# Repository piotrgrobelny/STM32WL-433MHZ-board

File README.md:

# STM32WL-433MHZ-board
STM32WL developer board with RF antenna. The board is made to work with LoRa, GFSK, GMSK, BPSK in 433MHz frequency. 
STM32WLE5CCU6 with single code Cortex-M4 256KB Flash and 64KB RAM is used. The project is based on different boards like Nucleo and BB-STM32WL. Feel free to use, but i don't promise that it will work. 

## Features
- STM32WLE5CCU6 Single code 32-bit Arm Cortex-M4
- RF transceiver 433MHz
- USB power supply
- SWD connector
- RESET button
- Two user buttons
- Two user leds
- Voltage regulator based on TLV70233
- Dimensions 5.2cm x 7.3cm

## Files description 
- `Board photos` 3D renders and PCB signal paths
- `KiCad` KiCad project with PCB, schematics, gerber files, list of elements and library of footprints
- `Documentantation` Project schematic in pdf, STM32WL datasheets and Nucleo and BB-STM32WL schematics

#### Front of PCB

#### Back of PCB

#### Upper signal path

#### Lower signal path

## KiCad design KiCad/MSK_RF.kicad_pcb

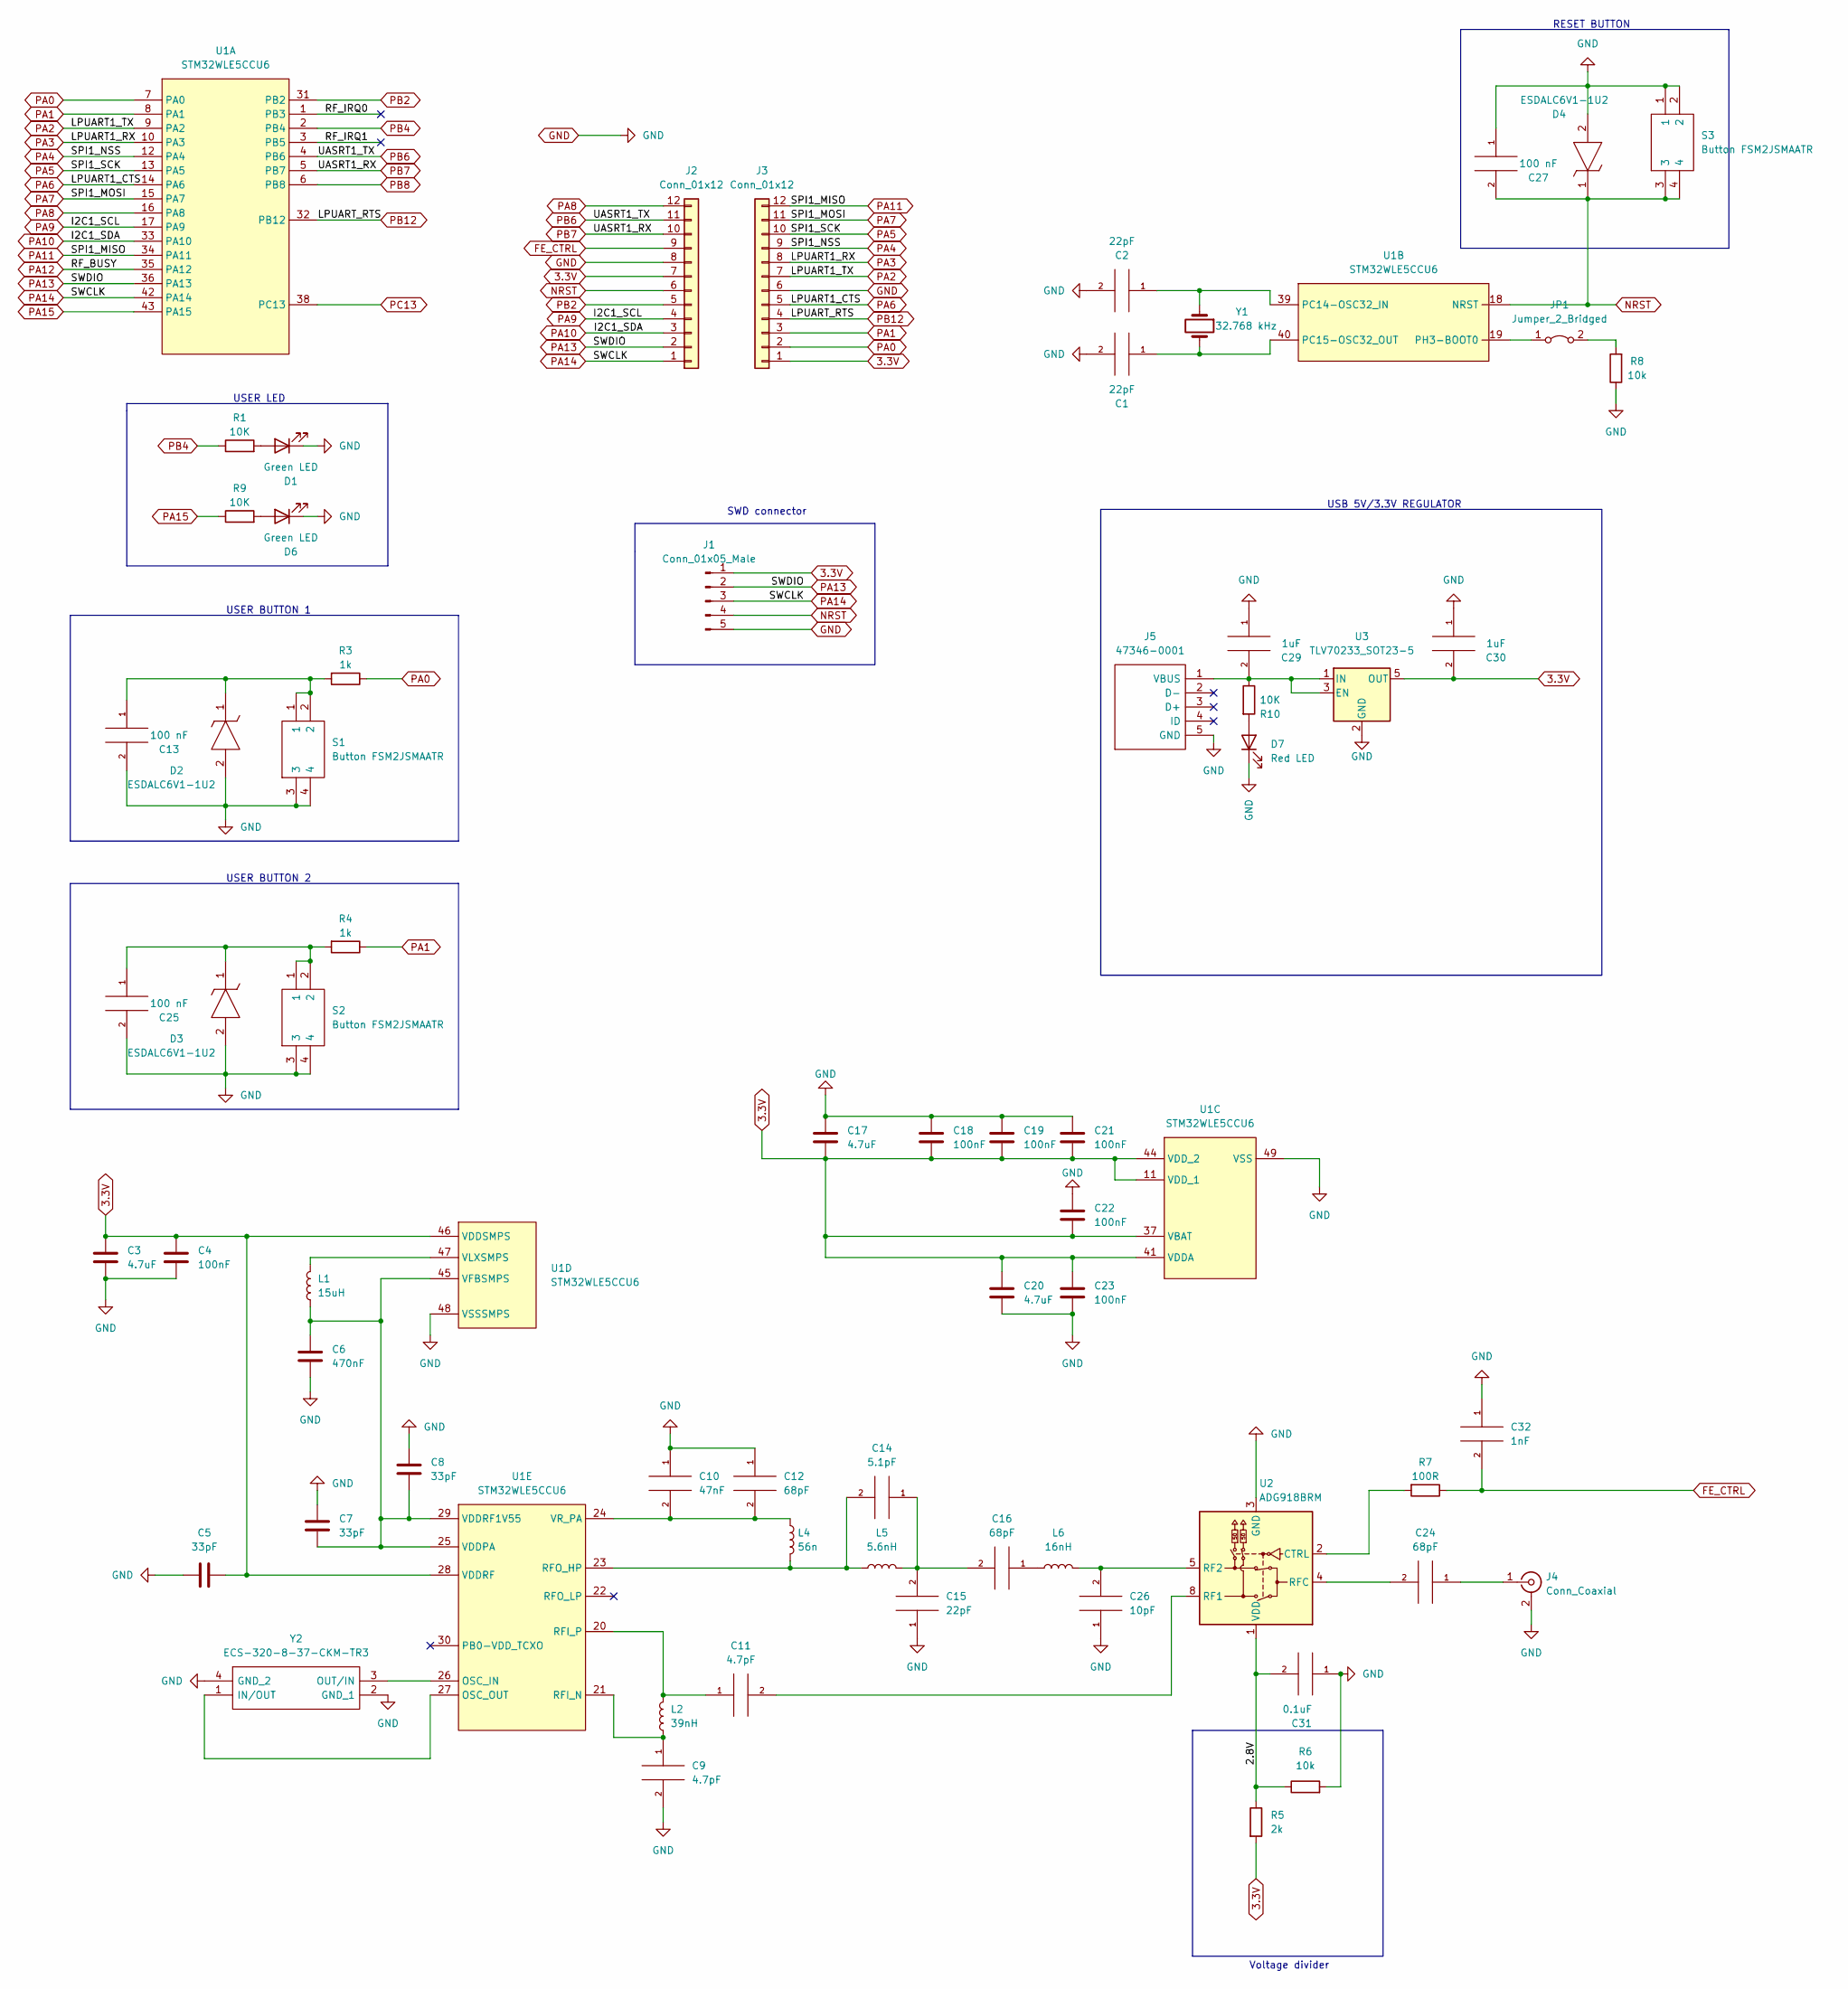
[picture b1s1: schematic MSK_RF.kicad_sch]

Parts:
C1, C2: 22pF; CP_Elec_3x5.3
C3, C17, C20: 4.7uF; C_0603_1608Metric_Pad1.08x0.95mm_HandSolder
C4, C18, C19, C21, C22, C23: 100nF; C_0603_1608Metric_Pad1.08x0.95mm_HandSolder
C5, C7, C8: 33pF; C_0603_1608Metric_Pad1.08x0.95mm_HandSolder
C6: 470nF; C_0603_1608Metric_Pad1.08x0.95mm_HandSolder
C9, C11: 4.7pF; C_0603_1608Metric_Pad1.08x0.95mm_HandSolder
C10: 47nF; C_0603_1608Metric_Pad1.08x0.95mm_HandSolder
C12, C16, C24: 68pF; C_0603_1608Metric_Pad1.08x0.95mm_HandSolder
C13, C25, C27: 100 nF; C_0603_1608Metric_Pad1.08x0.95mm_HandSolder
C14: 5.1pF; C_0603_1608Metric_Pad1.08x0.95mm_HandSolder
C15: 22pF; C_0603_1608Metric_Pad1.08x0.95mm_HandSolder
C26: 10pF; C_0603_1608Metric_Pad1.08x0.95mm_HandSolder
C29, C30: 1uF; C_0603_1608Metric_Pad1.08x0.95mm_HandSolder
C31: 0.1uF; C_0603_1608Metric_Pad1.08x0.95mm_HandSolder
C32: 1nF; C_0603_1608Metric_Pad1.08x0.95mm_HandSolder
D1, D6: Green LED; LED_0603_1608Metric_Pad1.05x0.95mm_HandSolder
D2, D3, D4: ESDALC6V1-1U2; ESDALC6V11U2; Mouser Part Number 511-ESDALC6V1-1U2
D7: Red LED; LED_0603_1608Metric_Pad1.05x0.95mm_HandSolder
J1: Conn_01x05_Male; PinHeader_1x05_P2.54mm_Vertical
J2, J3: Conn_01x12; PinSocket_1x12_P2.54mm_Vertical
J4: Conn_Coaxial; SMA_Molex_73251-1153_EdgeMount_Horizontal
J5: 47346-0001; Mouser Part Number 538-47346-0001
JP1: Jumper_2_Bridged; PinHeader_1x02_P2.54mm_Vertical
L1: 15uH; L_0603_1608Metric_Pad1.05x0.95mm_HandSolder
L2: 39nH; L_0603_1608Metric_Pad1.05x0.95mm_HandSolder
L4: 56n; L_0603_1608Metric_Pad1.05x0.95mm_HandSolder
L5: 5.6nH; L_0603_1608Metric_Pad1.05x0.95mm_HandSolder
L6: 16nH; L_0603_1608Metric_Pad1.05x0.95mm_HandSolder
R1, R9, R10: 10K; R_0603_1608Metric_Pad0.98x0.95mm_HandSolder
R3, R4: 1k; R_0603_1608Metric_Pad0.98x0.95mm_HandSolder
R5: 2k; R_0603_1608Metric_Pad0.98x0.95mm_HandSolder
R6, R8: 10k; R_0603_1608Metric_Pad0.98x0.95mm_HandSolder
R7: 100R; R_0603_1608Metric_Pad0.98x0.95mm_HandSolder
S1, S2, S3: Button FSM2JSMAATR; FSM2J_1; Mouser Part Number 506-FSM2JSMAATR
U1: STM32WLE5CCU6; QFN50P700X700X60-49N-D
U2: ADG918BRM; MSOP-8_3x3mm_P0.65mm
U3: TLV70233_SOT23-5; SOT-23-5
Y1: 32.768 kHz; ECX-31B
Y2: ECS-320-8-37-CKM-TR3; ECS320837CKMTR3; Mouser Part Number 520-ECS-320837CKMTR3

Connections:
3.3V: C3.1, C4.1, C5.1, C17.2, C18.2, C19.2, C20.1, C21.2, C22.2, C23.1, C30.2, J1.1, J2.7, J3.1, R5.2, U1.11 (VDD_1), U1.28 (VDDRF), U1.37 (VBAT), U1.41 (VDDA), U1.44 (VDD_2), U1.46 (VDDSMPS), U3.5 (OUT)
/2.8V: C31.2, R5.1, R6.1, U2.1 (VDD)
/RF_IRQ0: U1.1 (PB3)
/RF_IRQ1: U1.3 (PB5)
FE_CTRL: C32.2, J2.9, R7.1
GND: C1.2, C2.2, C3.2, C4.2, C5.2, C6.2, C7.1, C8.1, C9.2, C10.1, C12.1, C13.2, C15.1, C17.1, C18.1, C19.1, C20.2, C21.1, C22.1, C23.2, C25.2, C26.1, C27.1, C29.1, C30.1, C31.1, C32.1, D1.1 (K), D2.2, D3.2, D4.2, D6.1 (K), D7.1 (K), J1.5, J2.8, J3.6, J4.2 (Ext), J5.5 (GND), R6.2, R8.1, S1.3, S1.4, S2.3, S2.4, S3.1, S3.2, U1.48 (VSSSMPS), U1.49 (VSS), U2.3 (GND), U2.6 (GND), U2.7 (GND), U3.2 (GND), Y2.2 (GND_1), Y2.4 (GND_2)
NRST: C27.2, D4.1, J1.4, J2.6, S3.3, S3.4, U1.18 (NRST)
unnamed: C1.1, U1.40 (PC15-OSC32_OUT), Y1.2
unnamed: C2.1, U1.39 (PC14-OSC32_IN), Y1.1
unnamed: C6.1, C7.2, C8.2, L1.1, U1.25 (VDDPA), U1.29 (VDDRF1V55), U1.45 (VFBSMPS)
unnamed: C9.1, L2.1, U1.21 (RFI_N)
unnamed: C10.2, C12.2, L4.1, U1.24 (VR_PA)
unnamed: C11.1, L2.2, U1.20 (RFI_P)
unnamed: C11.2, U2.8 (RF1)
unnamed: C13.1, D2.1, R3.2, S1.1, S1.2
unnamed: C14.1, C15.2, C16.2, L5.2
unnamed: C14.2, L4.2, L5.1, U1.23 (RFO_HP)
unnamed: C16.1, L6.1
unnamed: C24.1, J4.1 (In)
unnamed: C24.2, U2.4 (RFC)
unnamed: C25.1, D3.1, R4.2, S2.1, S2.2
unnamed: C26.2, L6.2, U2.5 (RF2)
unnamed: C29.2, J5.1 (VBUS), R10.1, U3.1 (IN), U3.3 (EN)
unnamed: D1.2 (A), R1.2
unnamed: D6.2 (A), R9.2
unnamed: D7.2 (A), R10.2
unnamed: JP1.1 (A), U1.19 (PH3-BOOT0)
unnamed: JP1.2 (B), R8.2
unnamed: L1.2, U1.47 (VLXSMPS)
unnamed: R7.2, U2.2 (CTRL)
unnamed: U1.26 (OSC_IN), Y2.3 (OUT/IN)
unnamed: U1.27 (OSC_OUT), Y2.1 (IN/OUT)
PA0: J3.2, R3.1, U1.7 (PA0)
PA1: J3.3, R4.1, U1.8 (PA1)
PA2: J3.7, U1.9 (PA2)
PA3: J3.8, U1.10 (PA3)
PA4: J3.9, U1.12 (PA4)
PA5: J3.10, U1.13 (PA5)
PA6: J3.5, U1.14 (PA6)
PA7: J3.11, U1.15 (PA7)
PA8: J2.12, U1.16 (PA8)
PA9: J2.4, U1.17 (PA9)
PA10: J2.3, U1.33 (PA10)
PA11: J3.12, U1.34 (PA11)
PA12: U1.35 (PA12)
PA13: J1.2, J2.2, U1.36 (PA13)
PA14: J1.3, J2.1, U1.42 (PA14)
PA15: R9.1, U1.43 (PA15)
PB2: J2.5, U1.31 (PB2)
PB4: R1.1, U1.2 (PB4)
PB6: J2.11, U1.4 (PB6)
PB7: J2.10, U1.5 (PB7)
PB8: U1.6 (PB8)
PB12: J3.4, U1.32 (PB12)
PC13: U1.38 (PC13)

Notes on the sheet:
SWD connector
USER BUTTON 2
RESET BUTTON
USER LED
USB 5V/3.3V REGULATOR
USER BUTTON 1
Voltage divider

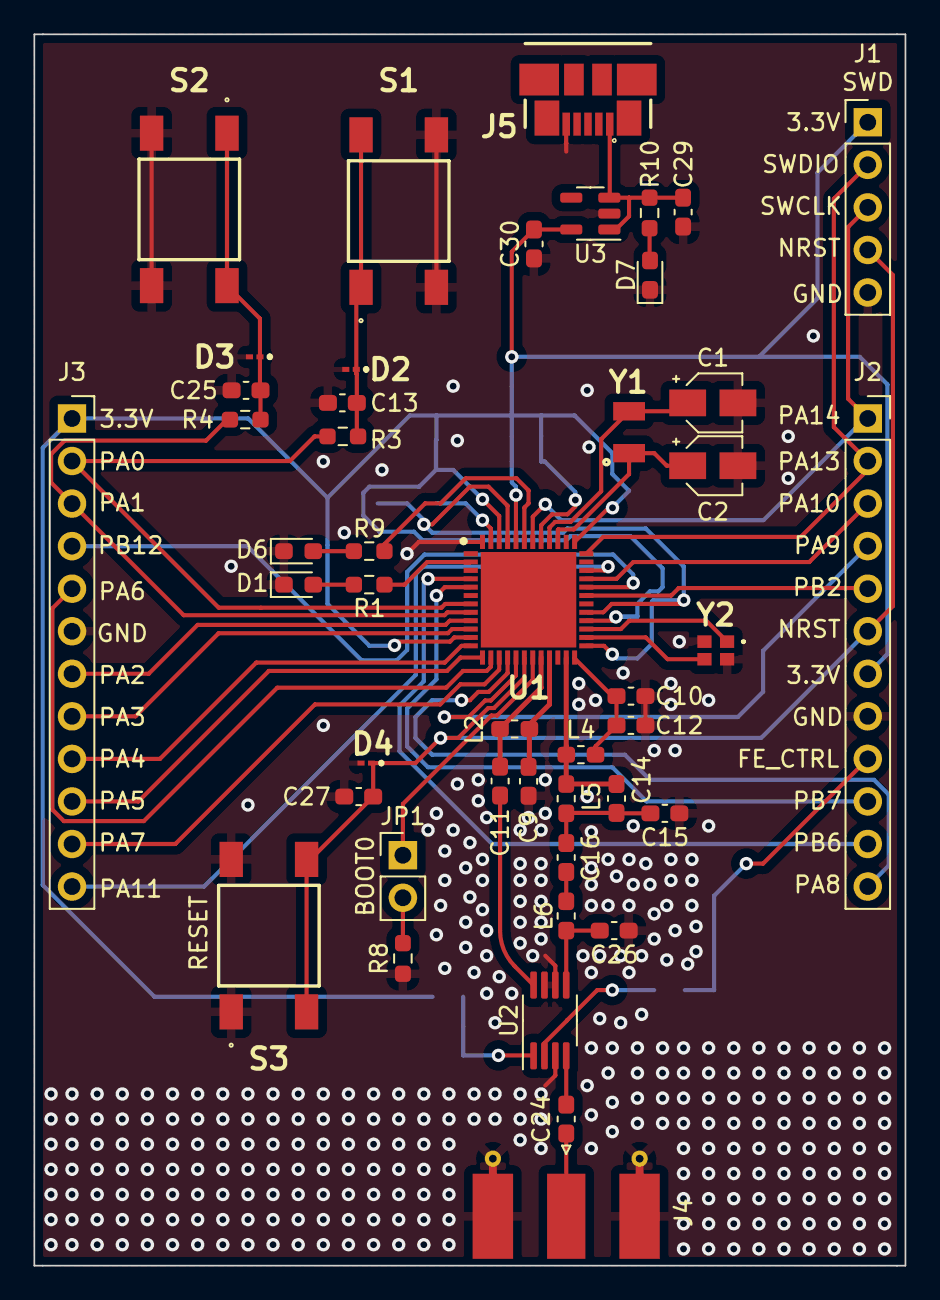
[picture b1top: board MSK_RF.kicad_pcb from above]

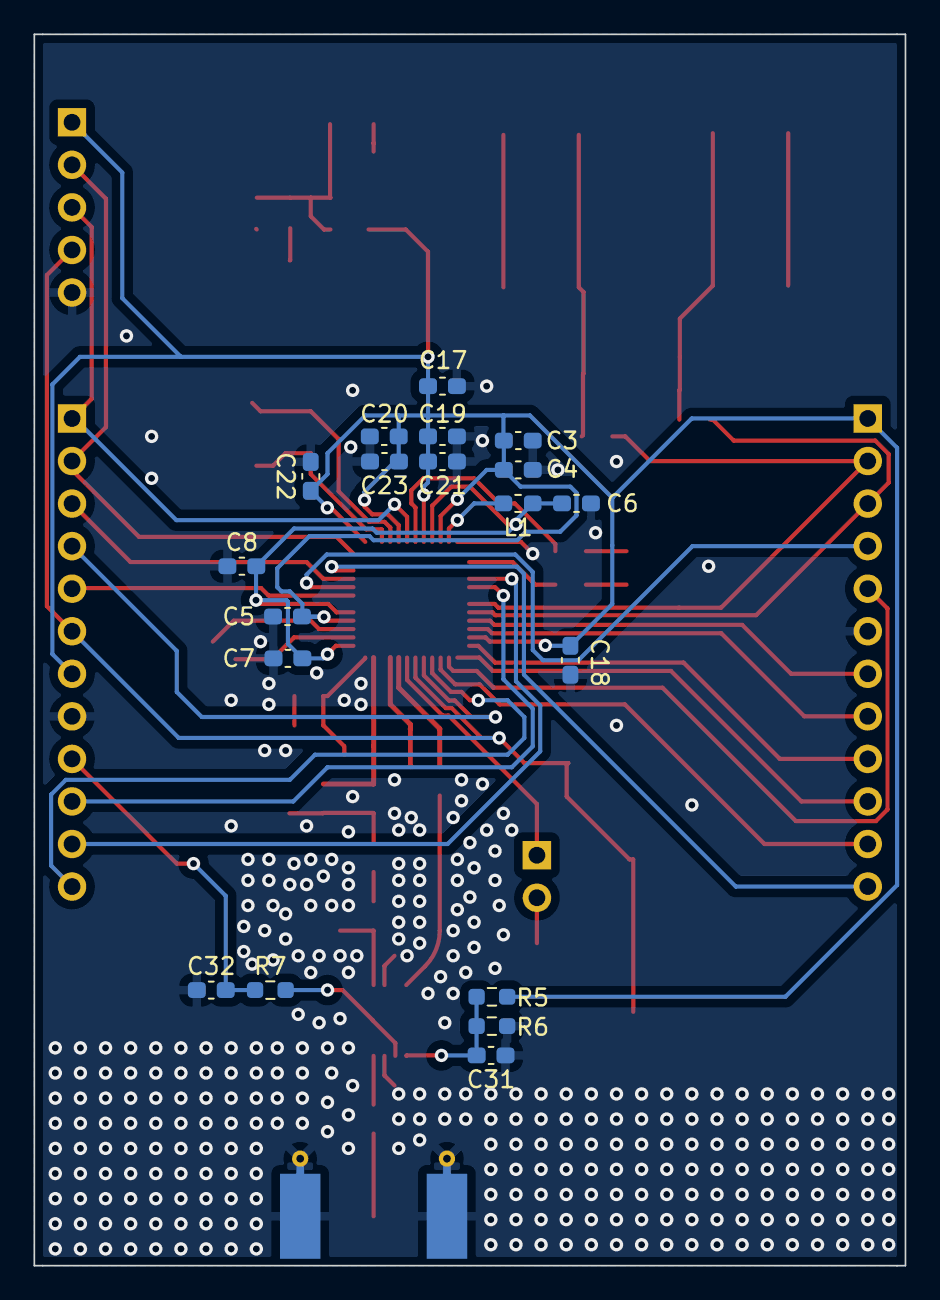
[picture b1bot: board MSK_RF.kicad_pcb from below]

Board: 2 copper layers, 52.0 x 73.5 mm, 65 parts (19 on the bottom side), 50 nets.

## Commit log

2022-04-15 Documentation and kicad schematics
2022-04-15 Second button
2022-04-16 added connectors footprint
2022-04-16 finished schematic with footprint
2022-04-17 patch
2022-04-19 library update
2022-04-19 Added i2c header
2022-04-21 pcb update
2022-04-21 almost finished pcb
2022-04-25 finished pcb
2022-04-25 added pin description
2022-04-25 diode description
2022-04-25 drc inspection solved
2022-04-26 fixed
2022-04-26 gerber files
2022-04-26 pin description
2022-04-28 vias update
2022-05-19 documentation and description
2022-05-19 pcb signal path
